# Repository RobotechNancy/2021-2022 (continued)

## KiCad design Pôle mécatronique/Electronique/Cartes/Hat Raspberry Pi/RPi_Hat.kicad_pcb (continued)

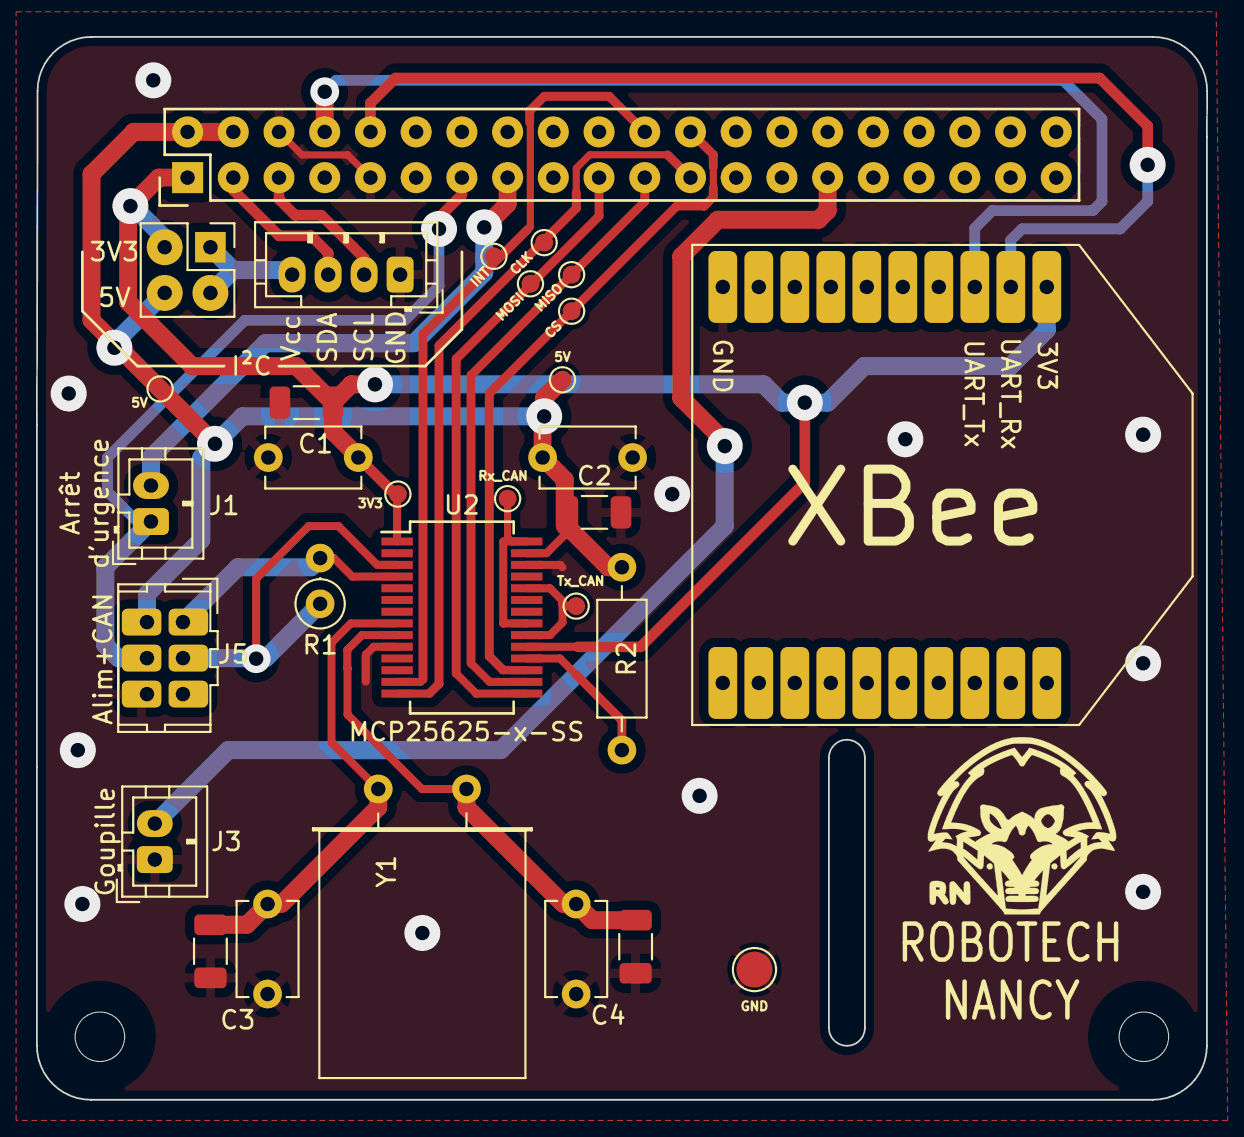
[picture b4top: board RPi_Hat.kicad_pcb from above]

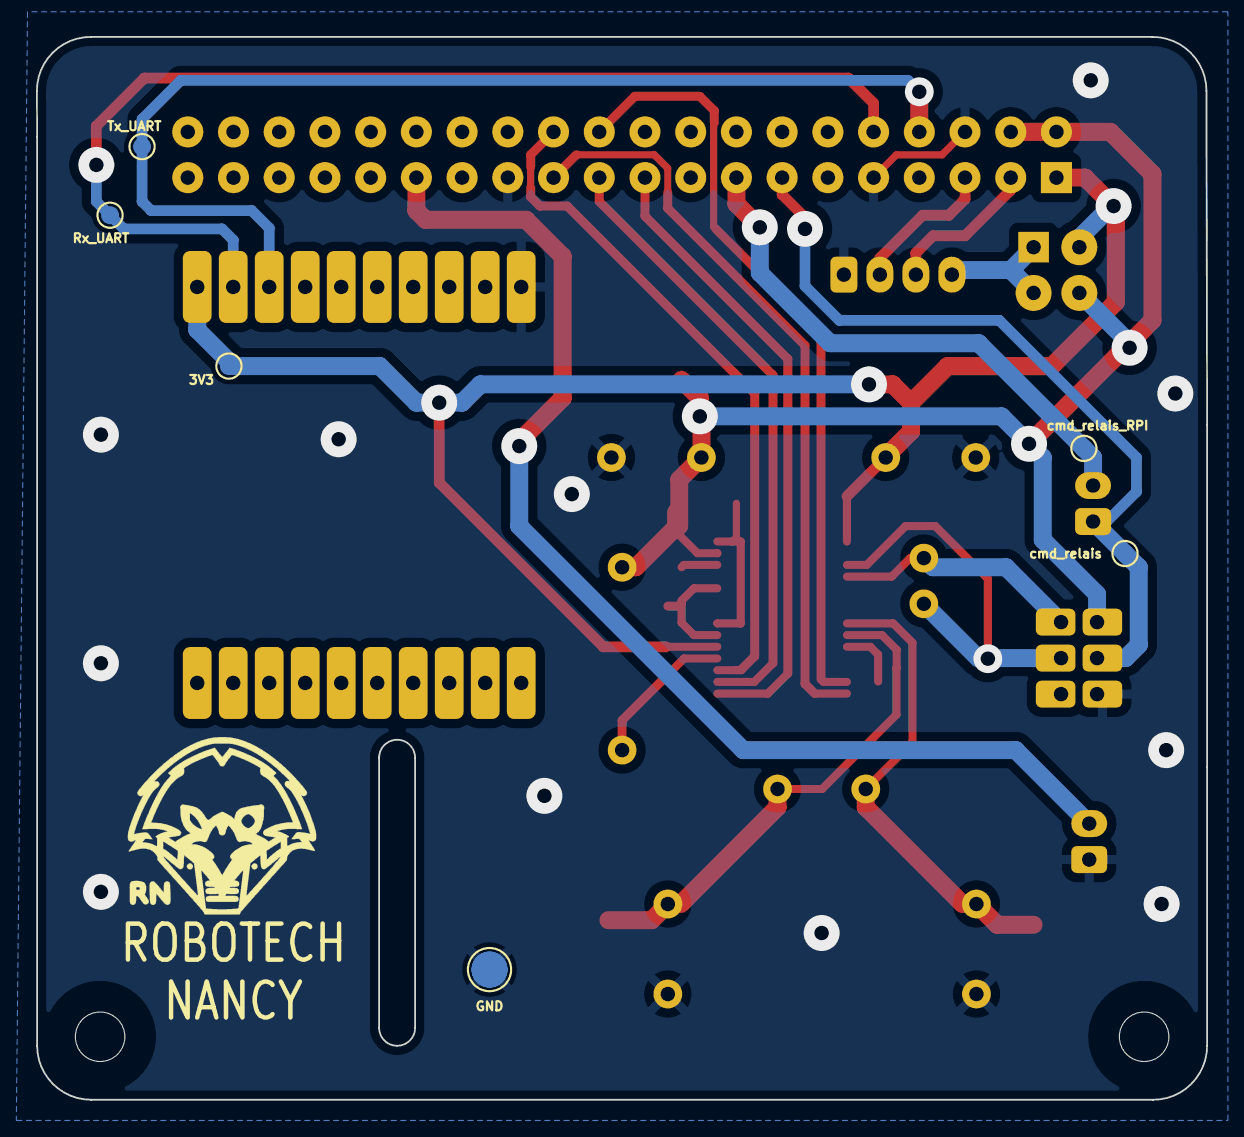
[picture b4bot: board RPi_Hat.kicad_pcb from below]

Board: 2 copper layers, 65.0 x 59.0 mm, 32 parts (6 on the bottom side), 23 nets.

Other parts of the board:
Test_INT: TestPoint_Pad_D1.0mm

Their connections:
INT: Test_INT.8; also elsewhere on the board

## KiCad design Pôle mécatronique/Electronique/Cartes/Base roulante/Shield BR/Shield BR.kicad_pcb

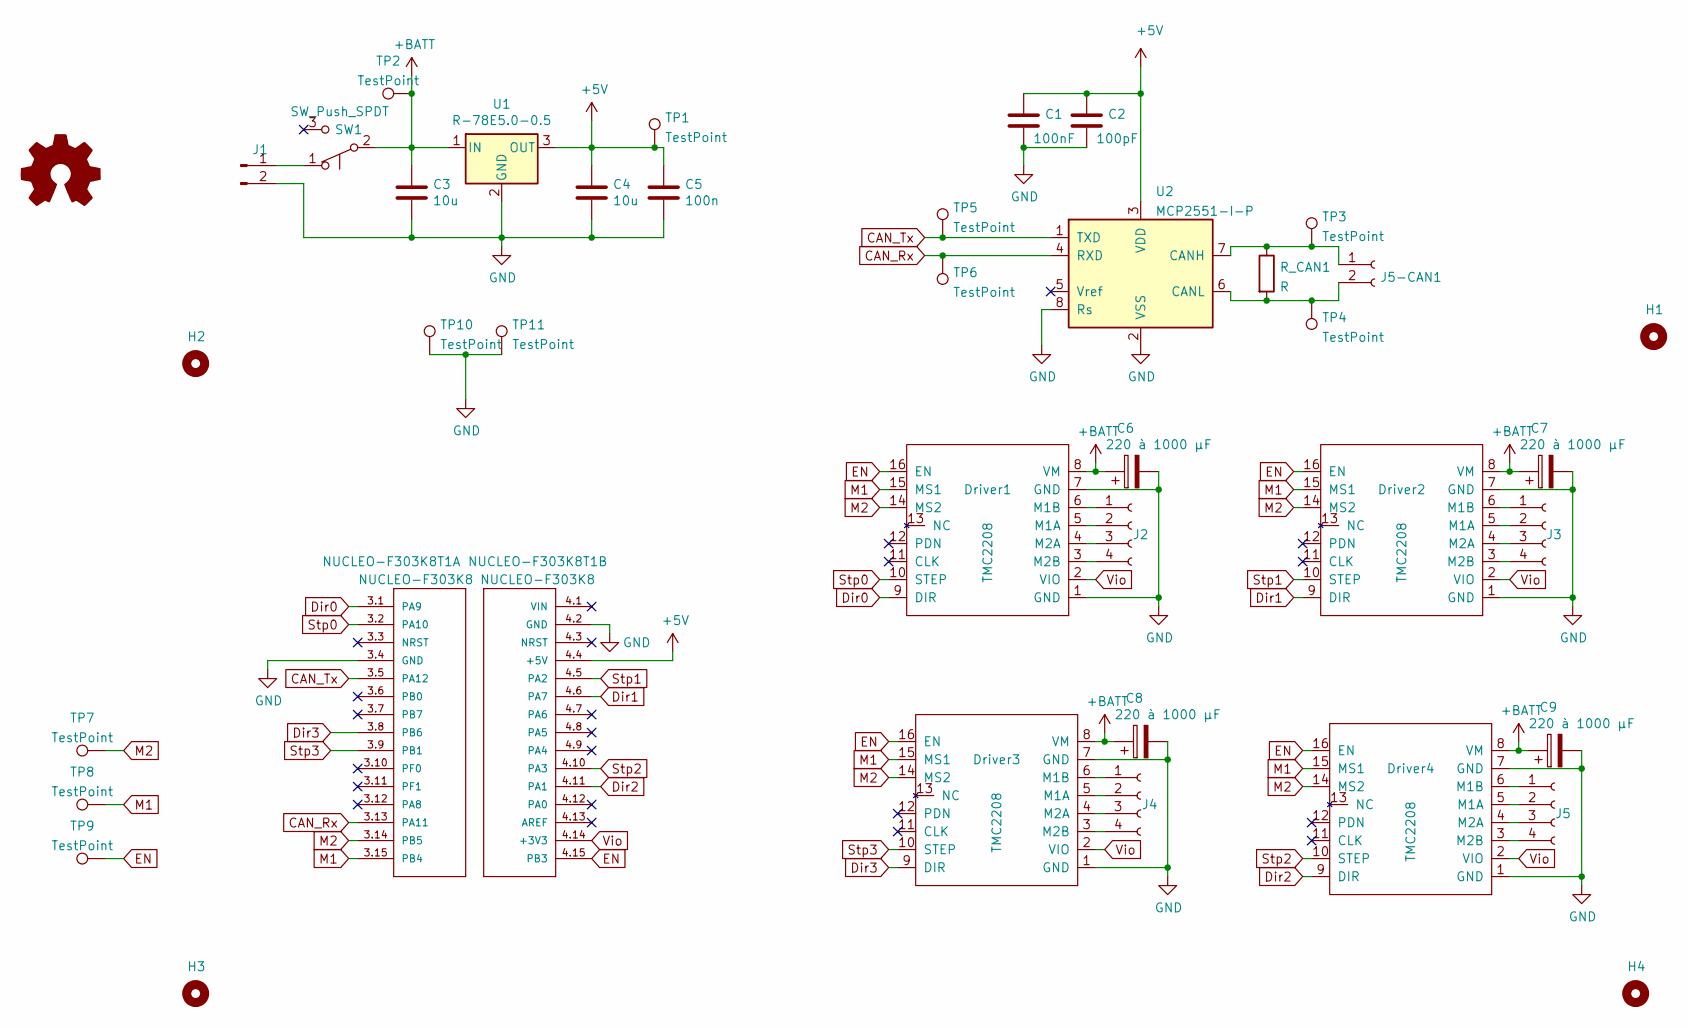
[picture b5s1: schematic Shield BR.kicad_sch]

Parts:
C1: 100nF; C_1206_3216Metric_Pad1.33x1.80mm_HandSolder
C2: 100pF; C_1206_3216Metric_Pad1.33x1.80mm_HandSolder
C3, C4: 10u; C_1206_3216Metric_Pad1.33x1.80mm_HandSolder
C5: 100n; C_1206_3216Metric_Pad1.33x1.80mm_HandSolder
C6, C7, C8, C9: 220 à 1000 µF; C_Elec_8x10.2
Driver1, Driver2, Driver3, Driver4: TMC2208; MODULE_TMC2208_SILENTSTEPSTICK
H1, H2, H3, H4: MountingHole; MountingHole_2.2mm_M2_ISO7380
J1: Conn_01x04_Male; Alim_Cablée_2_fils
J2, J3, J4, J5: Conn_01x04_Female; PinSocket_1x04_P2.54mm_Vertical
J5-CAN1: Conn_01x02_Female; JST_PH_B2B-PH-K_1x02_P2.00mm_Vertical
NUCLEO-F303K8T1: NUCLEO-F303K8; MODULE_NUCLEO-F303K8
R_CAN1: R; R_Axial_DIN0207_L6.3mm_D2.5mm_P7.62mm_Horizontal
SW1: SW_Push_SPDT; Switch_3_Pin
TP1, TP2, TP3, TP4, TP5, TP6, TP7, TP8, TP9, TP10, TP11: TestPoint; TestPoint_Pad_D2.0mm
U1: R-78E5.0-0.5; Converter_DCDC_RECOM_R-78E-0.5_THT
U2: MCP2551-I-P; DIP-8_W7.62mm

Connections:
+5V: C1.1, C2.1, C4.1, C5.1, NUCLEO-F303K8T1.4.4 (+5V), TP1.1, U1.3 (OUT), U2.3 (VDD)
+BATT: C3.1, C6.1, C7.1, C8.1, C9.1, Driver1.8 (VM), Driver2.8 (VM), Driver3.8 (VM), Driver4.8 (VM), SW1.2 (B), TP2.1, U1.1 (IN)
CAN_Rx: NUCLEO-F303K8T1.3.13 (PA11), TP6.1, U2.4 (RXD)
CAN_Tx: NUCLEO-F303K8T1.3.5 (PA12), TP5.1, U2.1 (TXD)
Dir0: Driver1.9 (DIR), NUCLEO-F303K8T1.3.1 (PA9)
Dir1: Driver2.9 (DIR), NUCLEO-F303K8T1.4.6 (PA7)
Dir2: Driver4.9 (DIR), NUCLEO-F303K8T1.4.11 (PA1)
Dir3: Driver3.9 (DIR), NUCLEO-F303K8T1.3.8 (PB6)
EN: Driver1.16 (EN), Driver2.16 (EN), Driver3.16 (EN), Driver4.16 (EN), NUCLEO-F303K8T1.4.15 (PB3), TP9.1
GND: C1.2, C2.2, C3.2, C4.2, C5.2, C6.2, C7.2, C8.2, C9.2, Driver1.1 (GND), Driver1.7 (GND), Driver2.1 (GND), Driver2.7 (GND), Driver3.1 (GND), Driver3.7 (GND), Driver4.1 (GND), Driver4.7 (GND), J1.2, NUCLEO-F303K8T1.3.4 (GND), NUCLEO-F303K8T1.4.2 (GND), TP10.1, TP11.1, U1.2 (GND), U2.2 (VSS), U2.8 (Rs)
M1: Driver1.15 (MS1), Driver2.15 (MS1), Driver3.15 (MS1), Driver4.15 (MS1), NUCLEO-F303K8T1.3.15 (PB4), TP8.1
M2: Driver1.14 (MS2), Driver2.14 (MS2), Driver3.14 (MS2), Driver4.14 (MS2), NUCLEO-F303K8T1.3.14 (PB5), TP7.1
unnamed: Driver1.3 (M2B), J2.4
unnamed: Driver1.4 (M2A), J2.3
unnamed: Driver1.5 (M1A), J2.2
unnamed: Driver1.6 (M1B), J2.1
unnamed: Driver2.3 (M2B), J3.4
unnamed: Driver2.4 (M2A), J3.3
unnamed: Driver2.5 (M1A), J3.2
unnamed: Driver2.6 (M1B), J3.1
unnamed: Driver3.3 (M2B), J4.4
unnamed: Driver3.4 (M2A), J4.3
unnamed: Driver3.5 (M1A), J4.2
unnamed: Driver3.6 (M1B), J4.1
unnamed: Driver4.3 (M2B), J5.4
unnamed: Driver4.4 (M2A), J5.3
unnamed: Driver4.5 (M1A), J5.2
unnamed: Driver4.6 (M1B), J5.1
unnamed: J1.1, SW1.1 (A)
unnamed: J5-CAN1.1, R_CAN1.1, TP3.1, U2.7 (CANH)
unnamed: J5-CAN1.2, R_CAN1.2, TP4.1, U2.6 (CANL)
Stp0: Driver1.10 (STEP), NUCLEO-F303K8T1.3.2 (PA10)
Stp1: Driver2.10 (STEP), NUCLEO-F303K8T1.4.5 (PA2)
Stp2: Driver4.10 (STEP), NUCLEO-F303K8T1.4.10 (PA3)
Stp3: Driver3.10 (STEP), NUCLEO-F303K8T1.3.9 (PB1)
Vio: Driver1.2 (VIO), Driver2.2 (VIO), Driver3.2 (VIO), Driver4.2 (VIO), NUCLEO-F303K8T1.4.14 (+3V3)

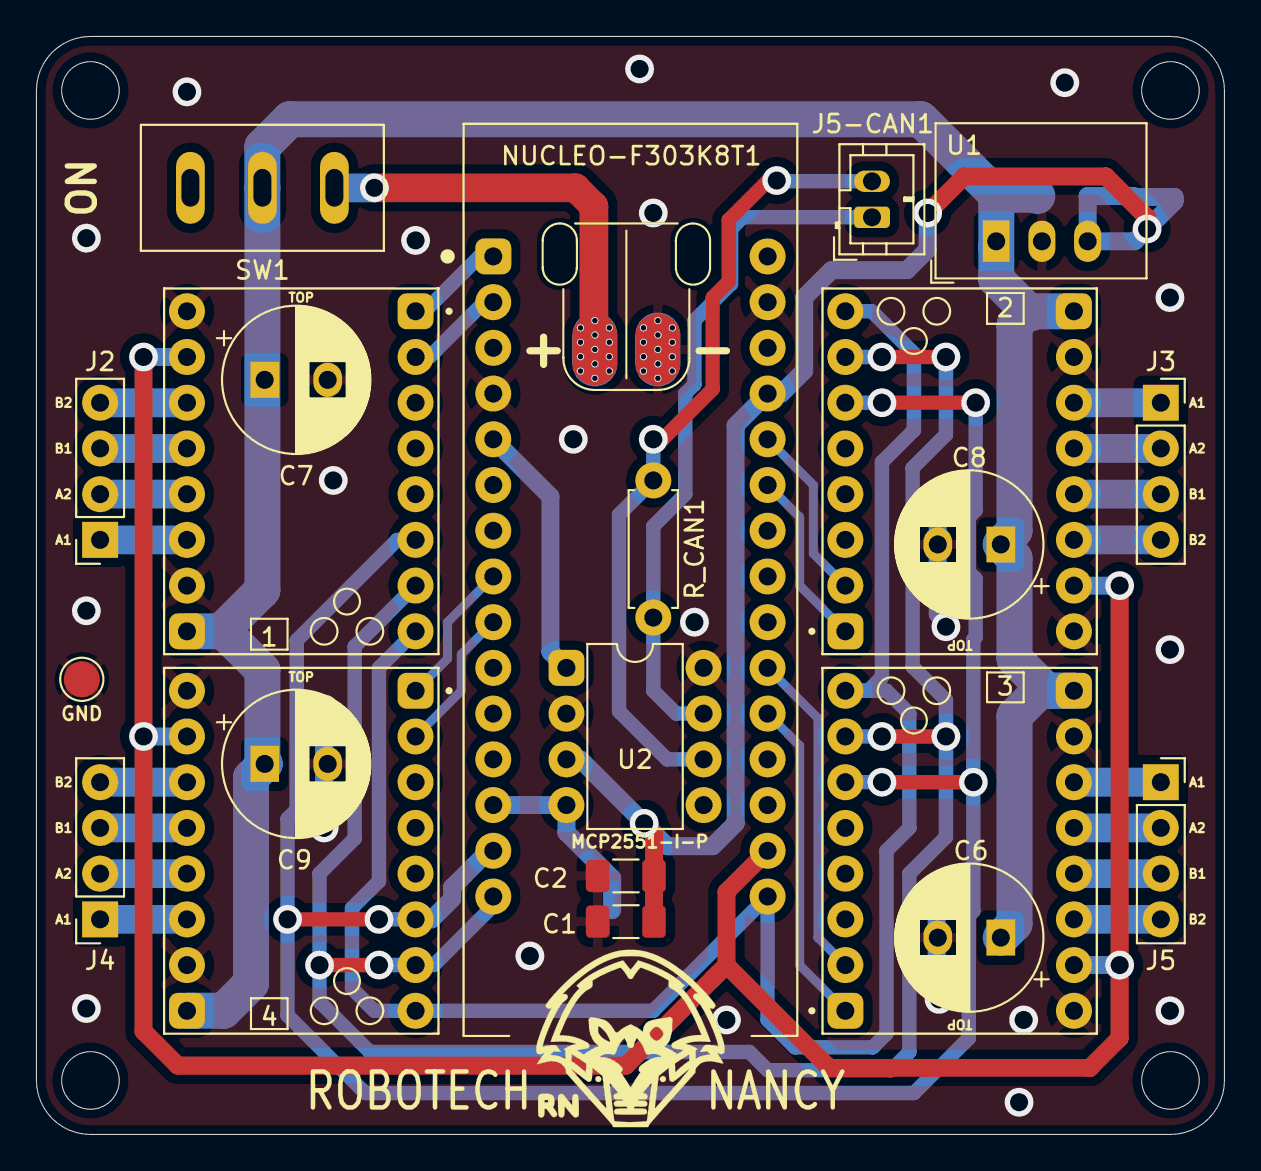
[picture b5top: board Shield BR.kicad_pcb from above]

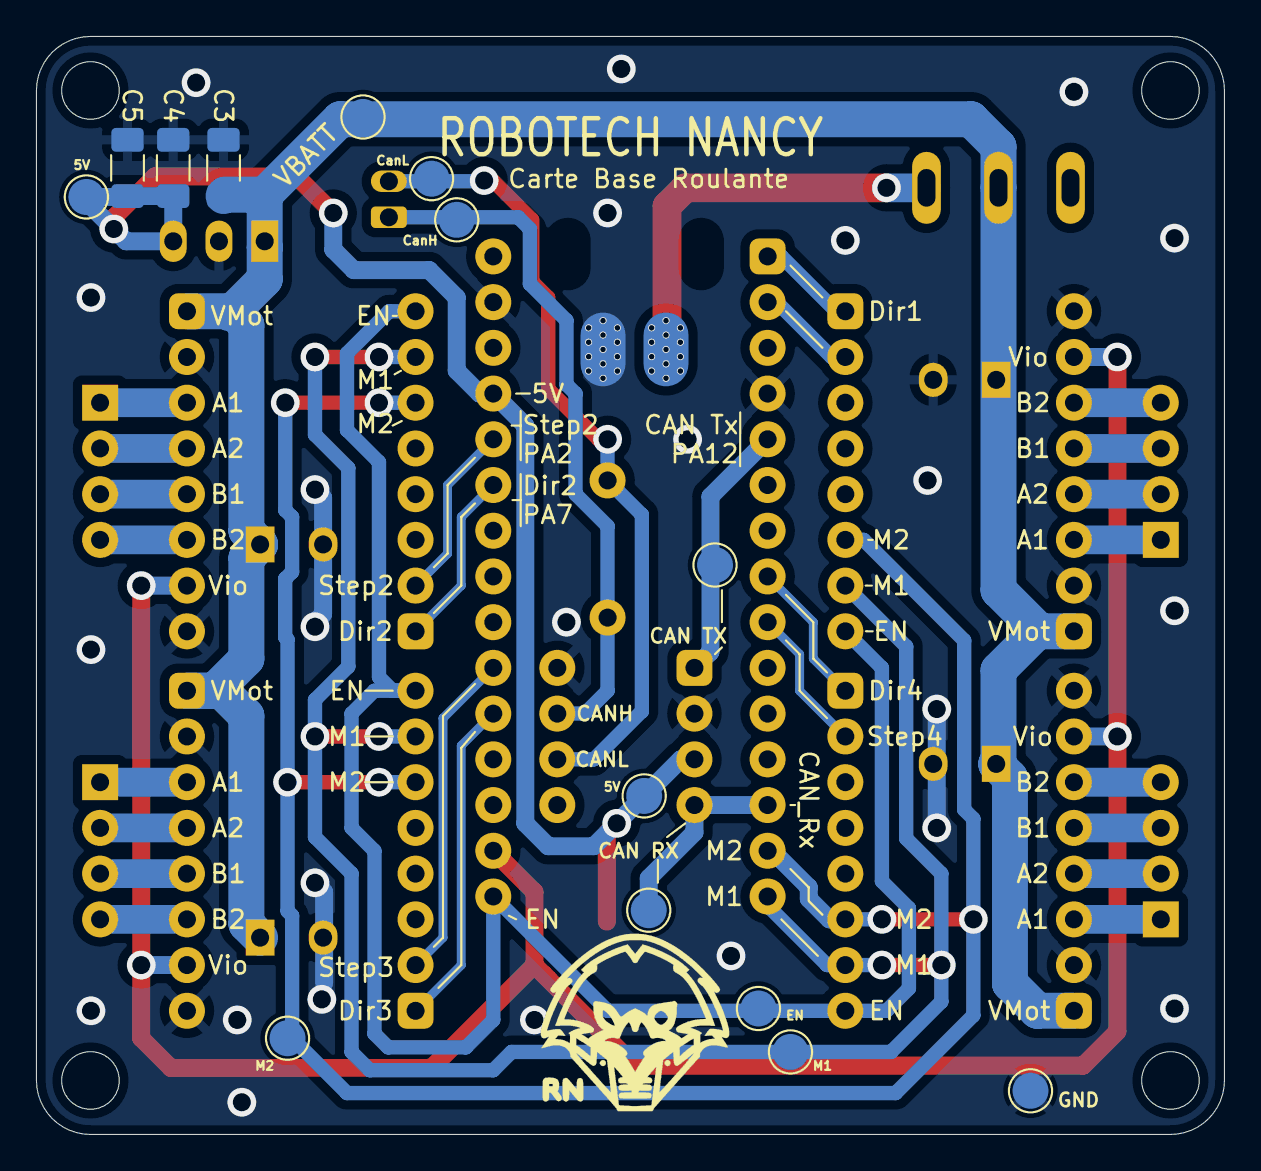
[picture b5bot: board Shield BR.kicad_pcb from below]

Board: 2 copper layers, 66.0 x 61.0 mm, 39 parts (13 on the bottom side), 36 nets.

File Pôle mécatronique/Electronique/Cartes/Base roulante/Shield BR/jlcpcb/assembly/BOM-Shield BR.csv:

Comment,Designator,Footprint,LCSC
Conn_01x04_Female,J2,PinSocket_1x04_P2.54mm_Vertical,
Conn_01x04_Female,J3,PinSocket_1x04_P2.54mm_Vertical,
Conn_01x04_Female,J5,PinSocket_1x04_P2.54mm_Vertical,
Conn_01x04_Female,J4,PinSocket_1x04_P2.54mm_Vertical,
TMC2208,Driver1,MODULE_TMC2208_SILENTSTEPSTICK,
TMC2208,Driver2,MODULE_TMC2208_SILENTSTEPSTICK,
TMC2208,Driver4,MODULE_TMC2208_SILENTSTEPSTICK,
TMC2208,Driver3,MODULE_TMC2208_SILENTSTEPSTICK,
R-78E5.0-0.5,U1,Converter_DCDC_RECOM_R-78E-0.5_THT,
SW_Push_SPDT,SW1,Switch_3_Pin,
Conn_01x04_Male,J1,Alim_Cablée_2_fils,
MountingHole,H2,MountingHole_2.2mm_M2_ISO7380,
MountingHole,H1,MountingHole_2.2mm_M2_ISO7380,
MountingHole,H4,MountingHole_2.2mm_M2_ISO7380,
MountingHole,H3,MountingHole_2.2mm_M2_ISO7380,
R,R_CAN1,R_Axial_DIN0207_L6.3mm_D2.5mm_P7.62mm_Horizontal,
220 à 1000 µF,C8,CP_Radial_D8.0mm_P3.50mm,
220 à 1000 µF,C6,CP_Radial_D8.0mm_P3.50mm,
220 à 1000 µF,C9,CP_Radial_D8.0mm_P3.50mm,
TestPoint,TP11,TestPoint_Pad_D2.0mm,
100pF,C2,C_1206_3216Metric_Pad1.33x1.80mm_HandSolder,
Conn_01x02_Female,J5-CAN1,JST_PH_B2B-PH-K_1x02_P2.00mm_Vertical,
220 à 1000 µF,C7,CP_Radial_D8.0mm_P3.50mm,
MCP2551-I-P,U2,DIP-8_W7.62mm,
100nF,C1,C_1206_3216Metric_Pad1.33x1.80mm_HandSolder,
TestPoint,TP5,TestPoint_Pad_D2.0mm,
TestPoint,TP9,TestPoint_Pad_D2.0mm,
TestPoint,TP7,TestPoint_Pad_D2.0mm,
10u,C4,C_1206_3216Metric_Pad1.33x1.80mm_HandSolder,
TestPoint,TP8,TestPoint_Pad_D2.0mm,
100n,C5,C_1206_3216Metric_Pad1.33x1.80mm_HandSolder,
TestPoint,TP10,TestPoint_Pad_D2.0mm,
TestPoint,TP2,TestPoint_Pad_D2.0mm,
TestPoint,TP1,TestPoint_Pad_D2.0mm,
TestPoint,TP3,TestPoint_Pad_D2.0mm,
TestPoint,TP6,TestPoint_Pad_D2.0mm,
TestPoint,TP4,TestPoint_Pad_D2.0mm,
10u,C3,C_1206_3216Metric_Pad1.33x1.80mm_HandSolder,

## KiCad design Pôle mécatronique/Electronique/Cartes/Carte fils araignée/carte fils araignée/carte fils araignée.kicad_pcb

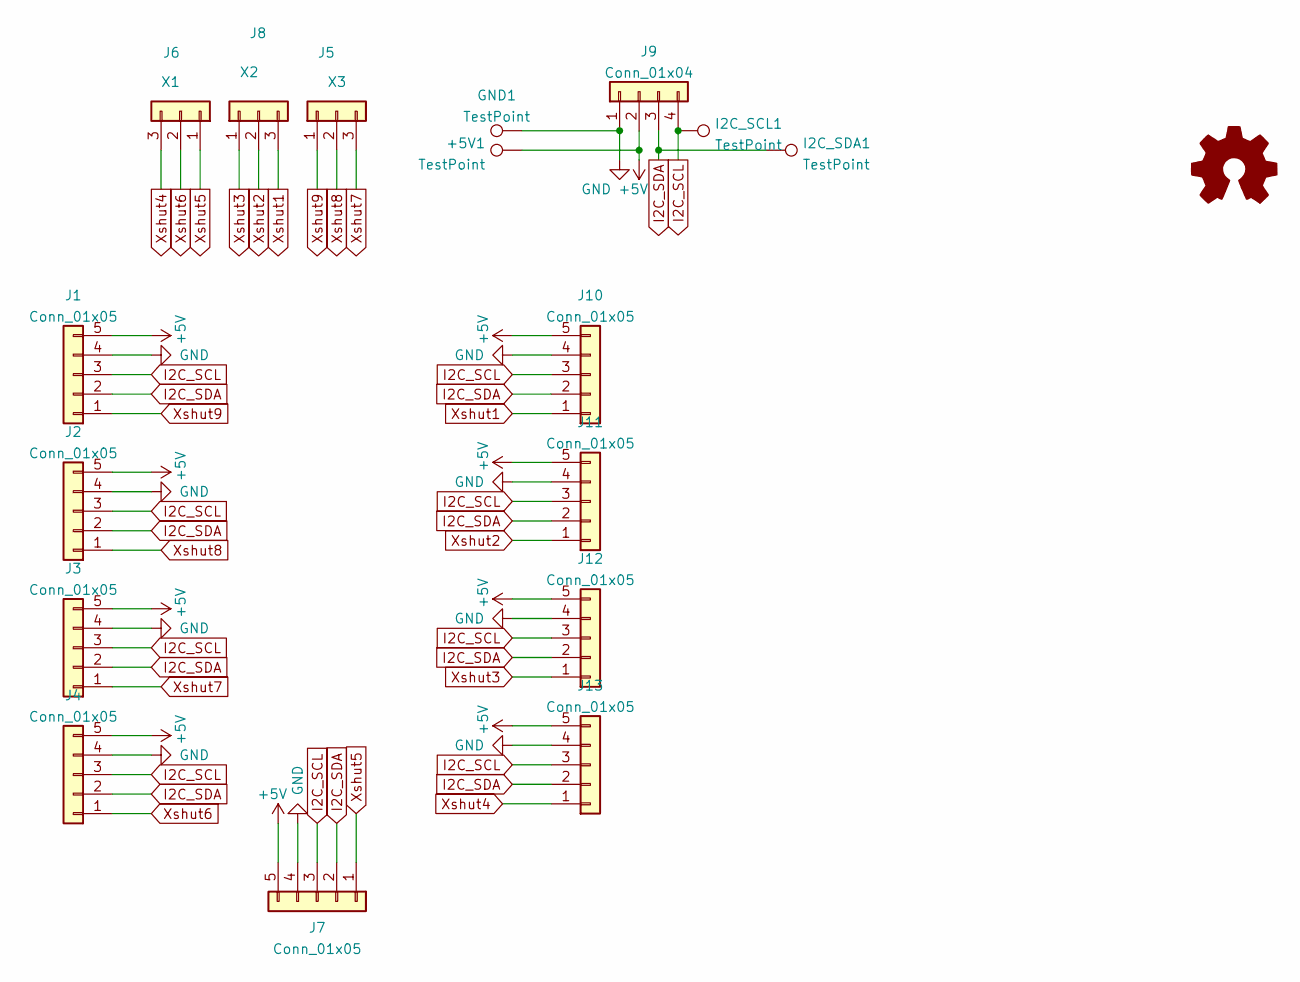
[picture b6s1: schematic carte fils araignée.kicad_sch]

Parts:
+5V1: TestPoint; TestPoint_Pad_D2.0mm
GND1: TestPoint; TestPoint_Pad_D2.0mm
I2C_SCL1, I2C_SDA1: TestPoint; TestPoint_Pad_D2.0mm
J1, J2, J3, J4, J10, J11, J12, J13: Conn_01x05; JST_EH_S5B-EH_1x05_P2.50mm_Horizontal
J5: X3; JST_EH_B3B-EH-A_1x03_P2.50mm_Vertical
J6: X1; JST_EH_B3B-EH-A_1x03_P2.50mm_Vertical
J7: Conn_01x05; JST_EH_B5B-EH-A_1x05_P2.50mm_Vertical
J8: X2; JST_EH_B3B-EH-A_1x03_P2.50mm_Vertical
J9: Conn_01x04; JST_EH_B4B-EH-A_1x04_P2.50mm_Vertical

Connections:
+5V: +5V1.1, J1.5, J2.5, J3.5, J4.5, J7.5, J9.2, J10.5, J11.5, J12.5, J13.5
GND: GND1.1, J1.4, J2.4, J3.4, J4.4, J7.4, J9.1, J10.4, J11.4, J12.4, J13.4
I2C_SCL: I2C_SCL1.1, J1.3, J2.3, J3.3, J4.3, J7.3, J9.4, J10.3, J11.3, J12.3, J13.3
I2C_SDA: I2C_SDA1.1, J1.2, J2.2, J3.2, J4.2, J7.2, J9.3, J10.2, J11.2, J12.2, J13.2
Xshut1: J8.3, J10.1
Xshut2: J8.2, J11.1
Xshut3: J8.1, J12.1
Xshut4: J6.3, J13.1
Xshut5: J6.1, J7.1
Xshut6: J4.1, J6.2
Xshut7: J3.1, J5.3
Xshut8: J2.1, J5.2
Xshut9: J1.1, J5.1

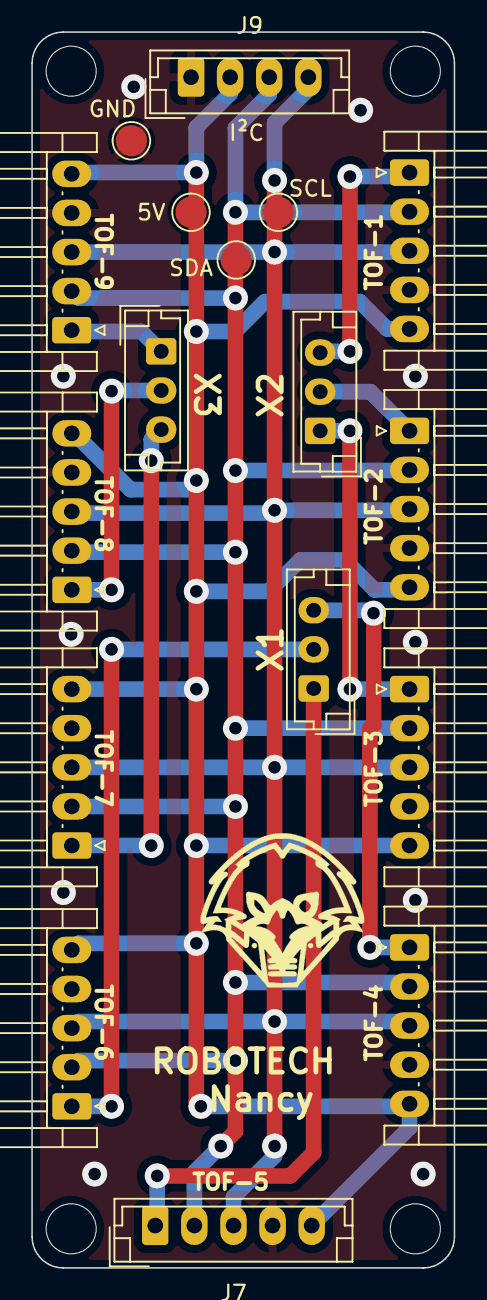
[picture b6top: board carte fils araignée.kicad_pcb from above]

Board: 2 copper layers, 27.0 x 79.0 mm, 17 parts (0 on the bottom side), 13 nets.

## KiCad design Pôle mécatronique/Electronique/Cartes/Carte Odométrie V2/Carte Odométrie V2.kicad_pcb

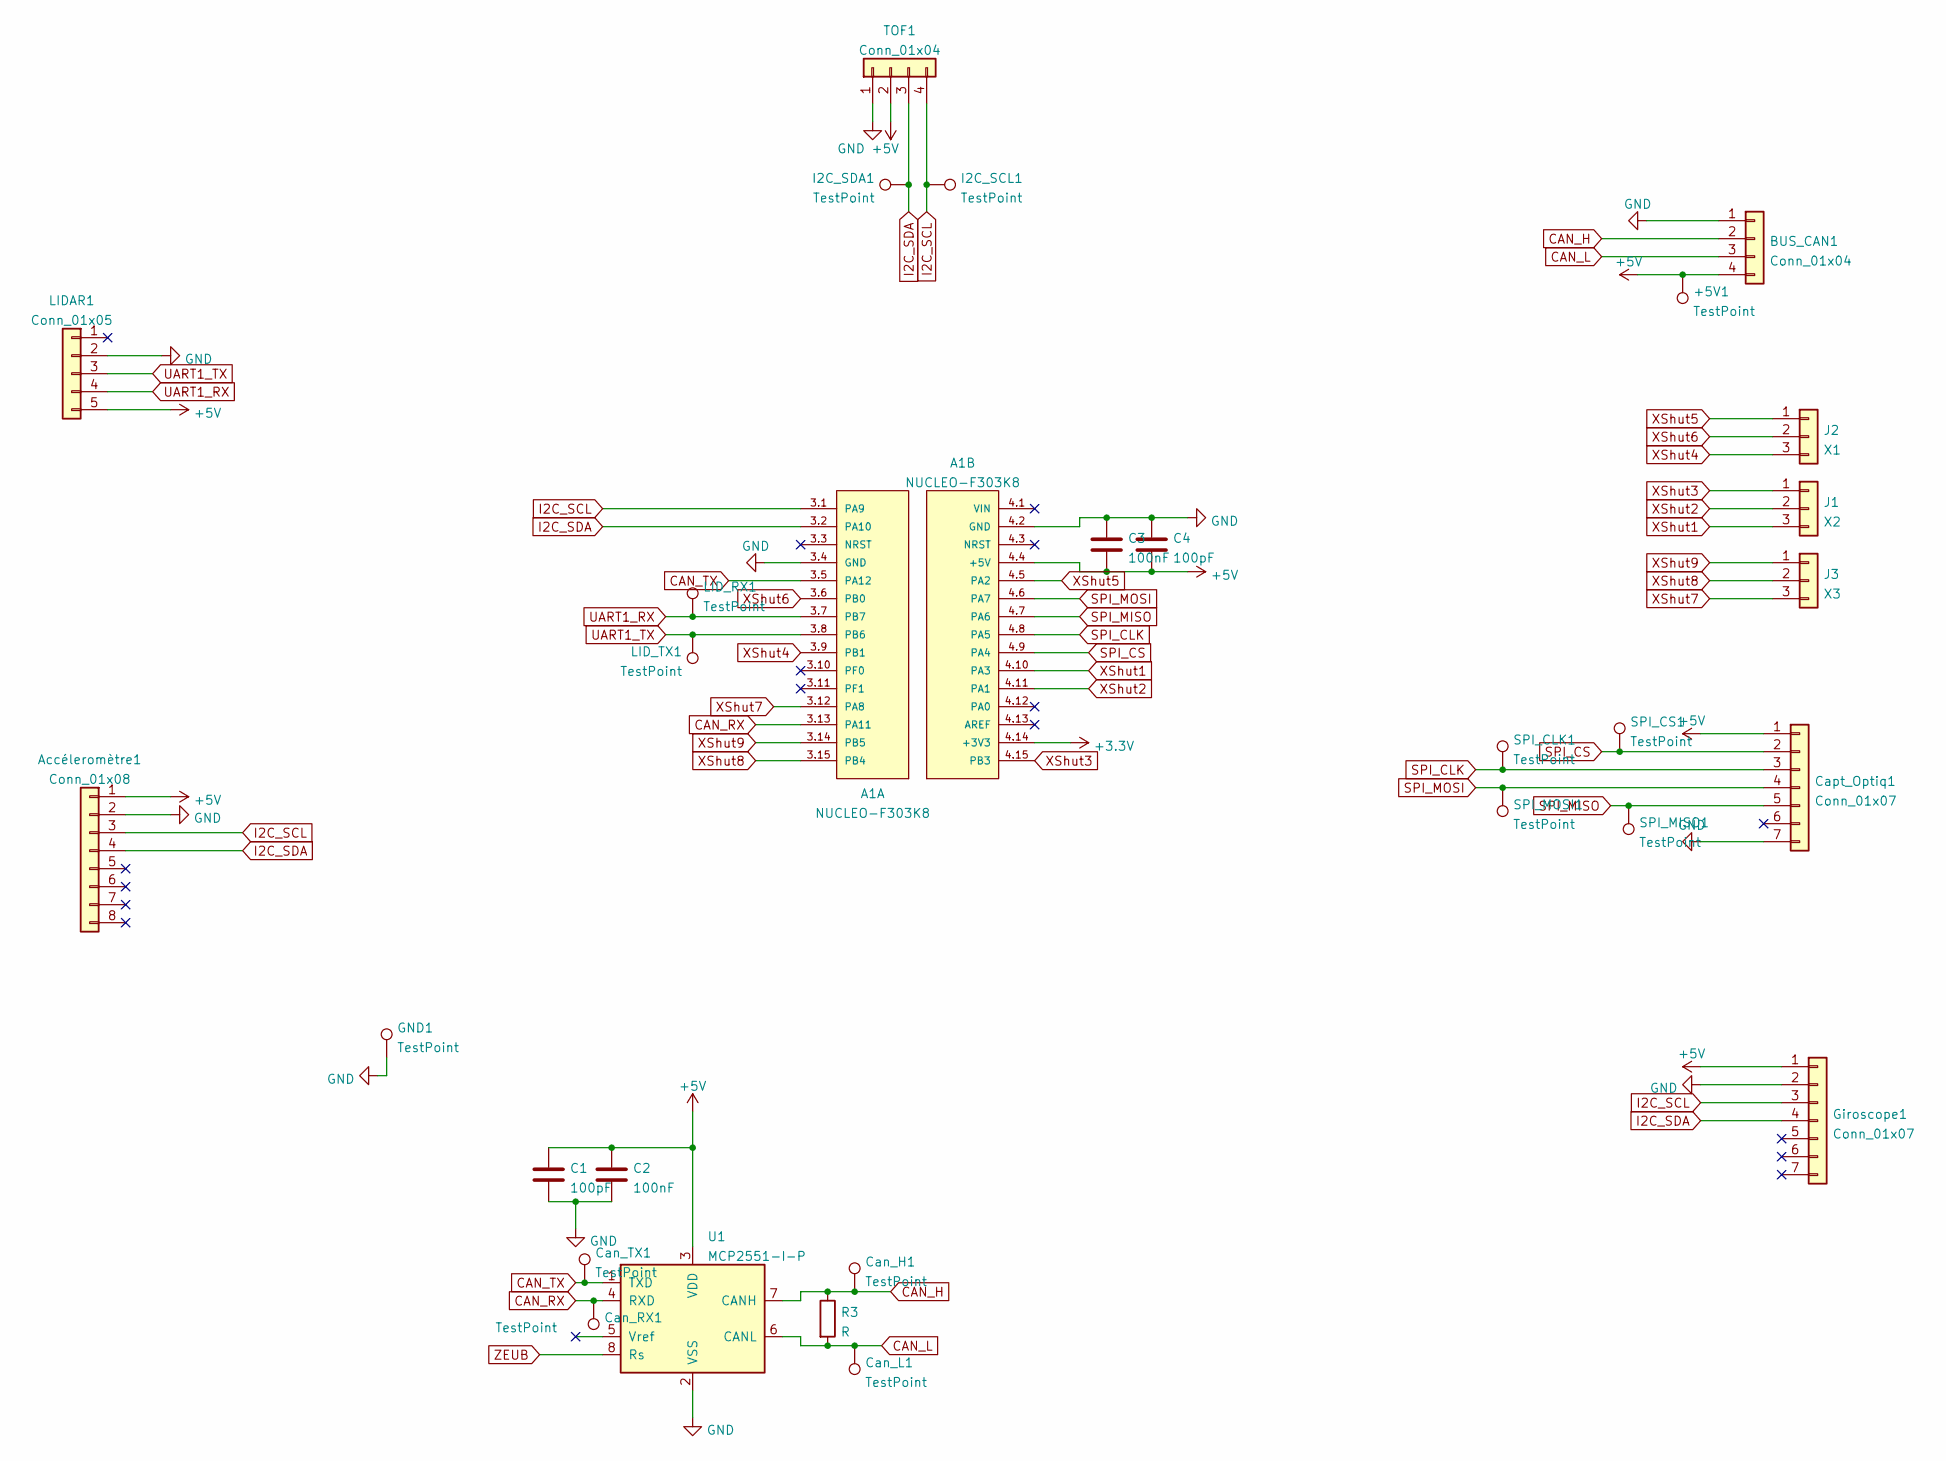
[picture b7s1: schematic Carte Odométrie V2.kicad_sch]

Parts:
+5V1: TestPoint; TestPoint_Pad_D2.0mm
A1: NUCLEO-F303K8; MODULE_NUCLEO-F303K8; PARTREV 3
Accéleromètre1: Conn_01x08; PinSocket_1x08_P2.54mm_Vertical
BUS_CAN1: Conn_01x04; JST_PH_B4B-PH-K_1x04_P2.00mm_Vertical
C1, C4: 100pF; C_1206_3216Metric
C2, C3: 100nF; C_1206_3216Metric
Can_H1: TestPoint; TestPoint_Pad_D2.0mm
Can_L1: TestPoint; TestPoint_Pad_D2.0mm
Can_RX1: TestPoint; TestPoint_Pad_D2.0mm
Can_TX1: TestPoint; TestPoint_Pad_D2.0mm
Capt_Optiq1: Conn_01x07; JST_PH_B7B-PH-K_1x07_P2.00mm_Vertical
GND1: TestPoint; TestPoint_Pad_D2.0mm
Giroscope1: Conn_01x07; PinSocket_1x07_P2.54mm_Vertical
I2C_SCL1, I2C_SDA1: TestPoint; TestPoint_Pad_D2.0mm
J1: X2; JST_EH_B3B-EH-A_1x03_P2.50mm_Vertical
J2: X1; JST_EH_B3B-EH-A_1x03_P2.50mm_Vertical
J3: X3; JST_EH_B3B-EH-A_1x03_P2.50mm_Vertical
LIDAR1: Conn_01x05; JST_PH_B5B-PH-K_1x05_P2.00mm_Vertical
LID_RX1: TestPoint; TestPoint_Pad_D2.0mm
LID_TX1: TestPoint; TestPoint_Pad_D2.0mm
R3: R; R_Axial_DIN0207_L6.3mm_D2.5mm_P10.16mm_Horizontal
SPI_CLK1: TestPoint; TestPoint_Pad_D2.0mm
SPI_CS1: TestPoint; TestPoint_Pad_D2.0mm
SPI_MISO1: TestPoint; TestPoint_Pad_D2.0mm
SPI_MOSI1: TestPoint; TestPoint_Pad_D2.0mm
TOF1: Conn_01x04; JST_PH_B4B-PH-K_1x04_P2.00mm_Vertical
U1: MCP2551-I-P; DIP-8_W7.62mm

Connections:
+3V3: A1.4.14 (+3V3)
+5V: +5V1.1, A1.4.4 (+5V), Accéleromètre1.1, BUS_CAN1.4, C1.1, C2.1, C3.2, C4.2, Capt_Optiq1.1, Giroscope1.1, LIDAR1.5, TOF1.2, U1.3 (VDD)
CAN_H: BUS_CAN1.2, Can_H1.1, R3.1, U1.7 (CANH)
CAN_L: BUS_CAN1.3, Can_L1.1, R3.2, U1.6 (CANL)
CAN_RX: A1.3.13 (PA11), Can_RX1.1, U1.4 (RXD)
CAN_TX: A1.3.5 (PA12), Can_TX1.1, U1.1 (TXD)
I2C_SCL: A1.3.1 (PA9), Accéleromètre1.3, Giroscope1.3, I2C_SCL1.1, TOF1.4
I2C_SDA: A1.3.2 (PA10), Accéleromètre1.4, Giroscope1.4, I2C_SDA1.1, TOF1.3
unnamed 8: Accéleromètre1.8; also elsewhere on the board
SPI_CLK: A1.4.8 (PA5), Capt_Optiq1.3, SPI_CLK1.1
SPI_CS: A1.4.9 (PA4), Capt_Optiq1.2, SPI_CS1.1
SPI_MISO: A1.4.7 (PA6), Capt_Optiq1.5, SPI_MISO1.1
SPI_MOSI: A1.4.6 (PA7), Capt_Optiq1.4, SPI_MOSI1.1
UART1_RX: A1.3.7 (PB7), LIDAR1.4, LID_RX1.1
UART1_TX: A1.3.8 (PB6), LIDAR1.3, LID_TX1.1
XShut1: A1.4.10 (PA3), J1.3
XShut2: A1.4.11 (PA1), J1.2
XShut3: A1.4.15 (PB3), J1.1
XShut4: A1.3.9 (PB1), J2.3
XShut5: A1.4.5 (PA2), J2.1
XShut6: A1.3.6 (PB0), J2.2
XShut7: A1.3.12 (PA8), J3.3
XShut8: A1.3.15 (PB4), J3.2
XShut9: A1.3.14 (PB5), J3.1

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
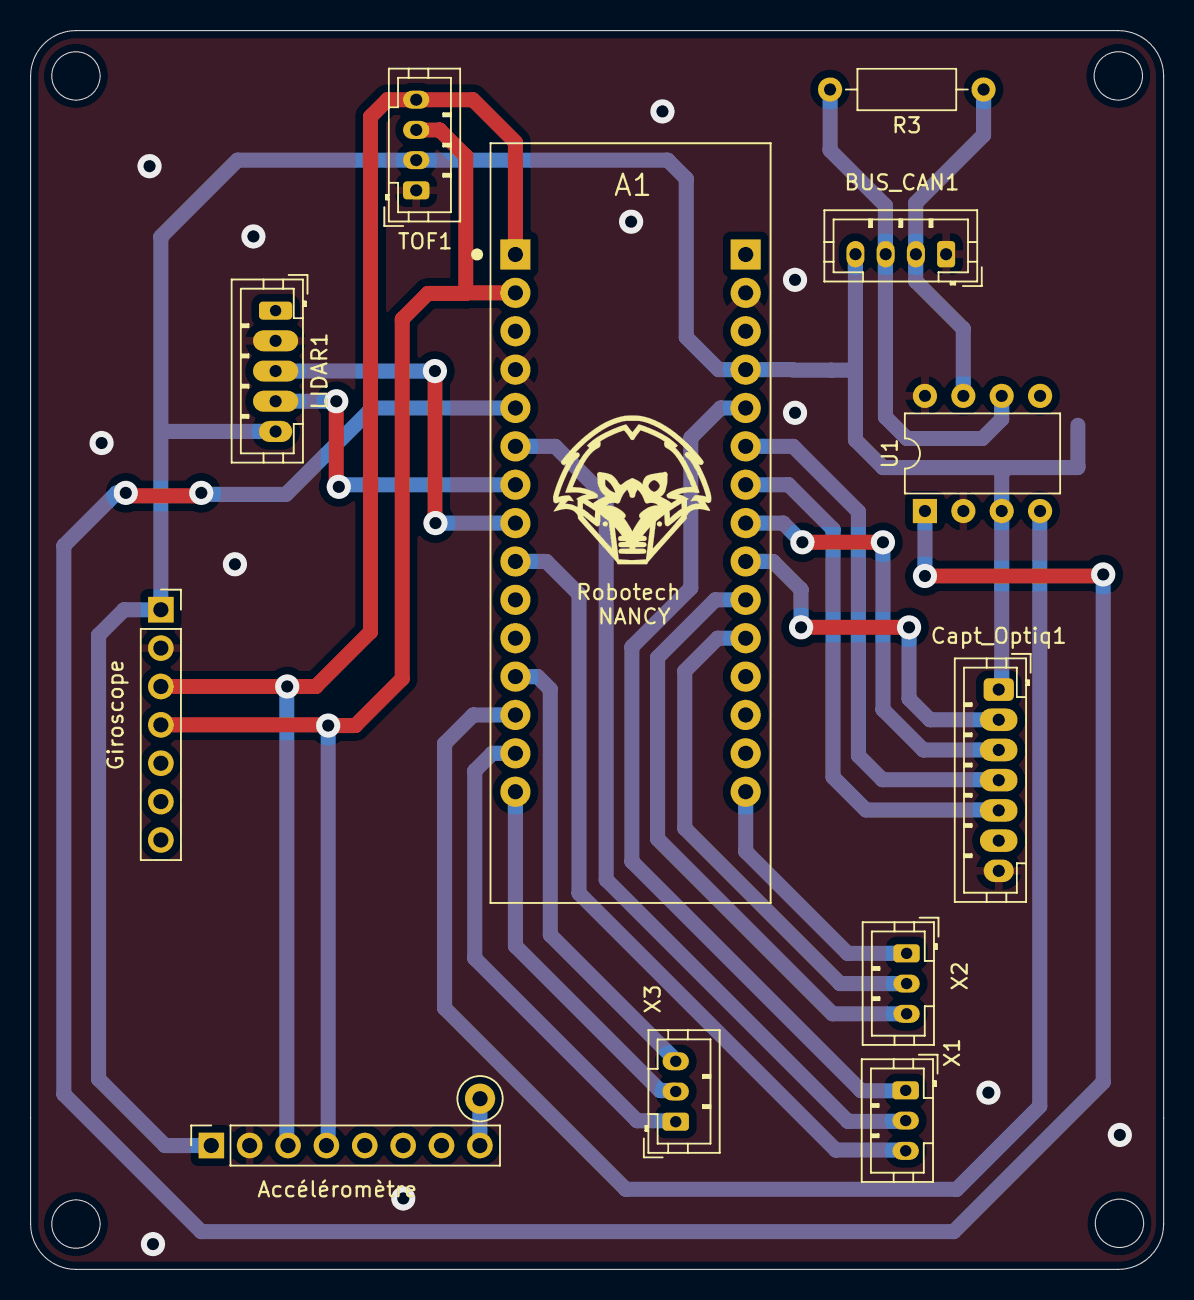
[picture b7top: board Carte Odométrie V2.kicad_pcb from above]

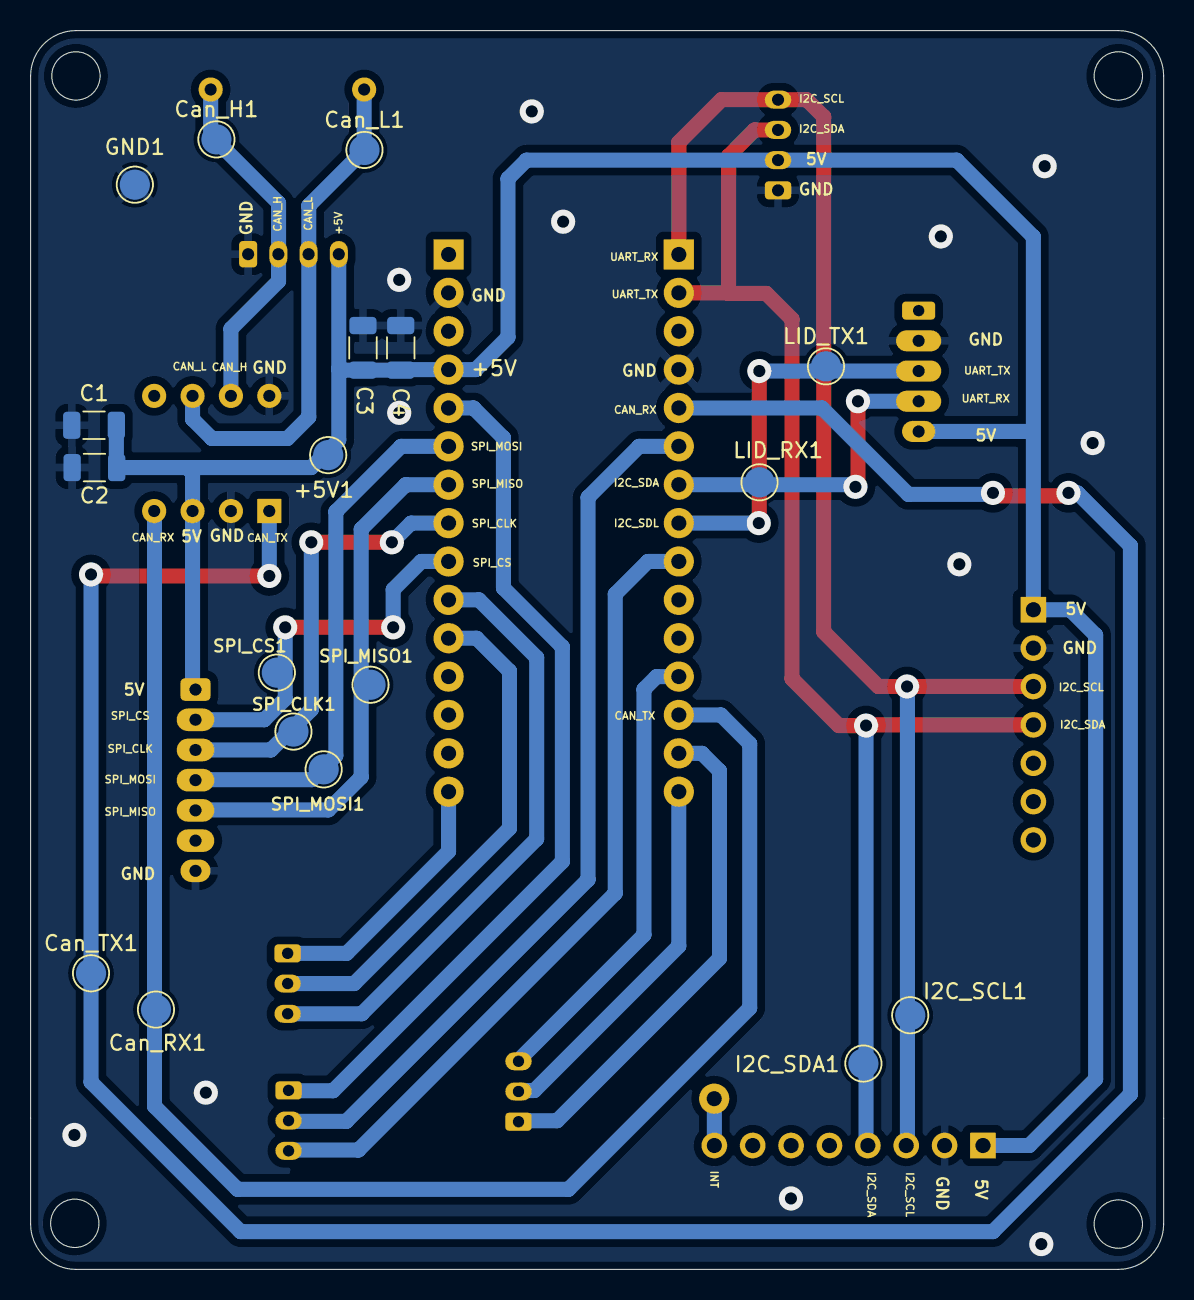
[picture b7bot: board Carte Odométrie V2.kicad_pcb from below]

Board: 2 copper layers, 75.0 x 82.0 mm, 35 parts (22 on the bottom side), 24 nets.

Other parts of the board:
REF: MountingHole_3.2mm_M3
REF#2, REF#3, REF#4: MountingHole_3.2mm_M3
TP1: INT; TestPoint_Loop_D2.50mm_Drill1.0mm

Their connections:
unnamed 8: TP1.1; also elsewhere on the board

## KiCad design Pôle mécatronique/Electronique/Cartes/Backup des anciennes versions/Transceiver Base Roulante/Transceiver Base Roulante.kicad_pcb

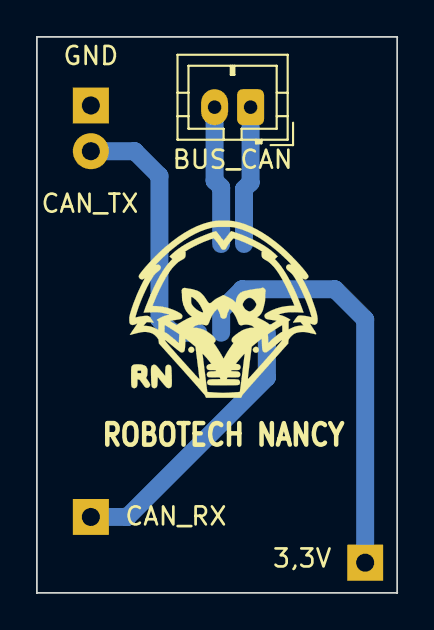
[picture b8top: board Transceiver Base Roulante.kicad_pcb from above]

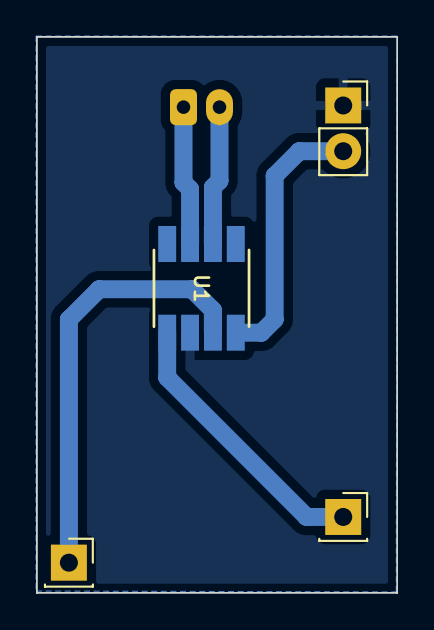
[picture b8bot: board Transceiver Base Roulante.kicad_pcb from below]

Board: 2 copper layers, 20.0 x 30.9 mm, 5 parts (4 on the bottom side), 6 nets.

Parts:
3,3V: Conn_01x01; PinSocket_1x01_P2.54mm_Vertical
BUS_CAN: Conn_01x02; JST_PH_B2B-PH-K_1x02_P2.00mm_Vertical
CAN_RX: Conn_01x01; PinSocket_1x01_P2.54mm_Vertical
GND: Conn_01x02; PinSocket_1x02_P2.54mm_Vertical
U1: TCAN332; SO-8_S

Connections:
+3V3: 3,3V.1, U1.3 (VCC)
CAN_H: BUS_CAN.1, U1.7 (CANH)
CAN_L: BUS_CAN.2, U1.6 (CANL)
CAN_RX: CAN_RX.1, U1.1 (TXD)
CAN_TX: GND.2, U1.4 (RXD)
GND: GND.1, U1.2 (GND)
